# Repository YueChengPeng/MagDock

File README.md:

# MagDock: a modular and customizable tangible inputs interface 

# OVERVIEW

## One Sentence Explanation
A customizable and reconfigurable haptic modular input interface for computers.

## Problem being Solved
Interacting with computers nowadays, either via touchscreens or keyboards (which are basically all buttons) is __BORING__!

The vision is to develop a new input interface, which supports rich interaction inputs and can be configured to be used in various scenarios to boost user experience, promote working efficiency, spark creative expression, enable precise input, provide interesting haptic feedback, etc.

## The Proposed Solution

The input device consists of two parts: a base (left) and various tactile input components (right). To use, simply snap one input component onto the __receptor__ of the base, which can automatically identify the component and read real-time inputs from it.

This input device can be directly used with laptops, pads, phones, etc. But to meet the requirements for the TECHIN514 course, I made a mockup of the computer using Raspberry Pi. To demonstrate the input potentials, I used a drawing web app (using P5.js on the browser of the Raspberry Pi) as a demonstration to showcase the potential of my design in supporting creative expressions (To be more specific, the joystick component is used to move the brush, the slider to adjust the width of the brush, the rotary knob to change the brush color, and the switch to clear the canvas). 

This is just a glimpse of the application! __Other **potential applications** include software extension inputs (e.g. shortcuts in PS, AI, Figma), music controllers/synthesizers (e.g. volume, mix controls), tailored game controllers (e.g. joysticks), sleek controllers for your next robot, etc.

## Working Video
[https://youtu.be/ztausAnTfQE](https://youtu.be/ztausAnTfQE)

# SYSTEM ARCHITECTURE
Details on the sensor device and the display device be elaborated in later sections. This is an overview of how the system architecture looks like:

## Highlights
- _Digital signal processing algorithms_ (explained in the "SENSOR DEVICE" section) are implemented on the ESP32S3 to convert 3-axis magnetic field data to interaction data.
- _BLE communication_ is used between the ESP32S3 XIAO and Raspberry Pi 4B to send real-time interaction data.
- _Websocket communication_ is used to realize real-time bidirectional data communication between the front-end app and the backend Python server.

# SENSOR DEVICE
## BOM
- 1 * [TLV493D magnetometer](https://www.digikey.com/en/products/detail/infineon-technologies/TLV493DA1B6HTSA2/5891933?utm_adgroup=&utm_source=google&utm_medium=cpc&utm_campaign=PMax%20Shopping_Product_High%20ROAS%20Categories&utm_term=&utm_content=&gad_source=1&gclid=Cj0KCQiAwbitBhDIARIsABfFYIIhFqM7H84WtRHeHdwaDSvtmzkl_We-hbJ-xpQ3_GwyePpydjeioHoaAnVZEALw_wcB)
- 1 * [XIAO ESP32S3](https://www.seeedstudio.com/XIAO-ESP32S3-p-5627.html)
- 1 * [2000mAh Lipo battery](https://www.amazon.com/EEMB-2000mAh-Battery-Rechargeable-Connector/dp/B08214DJLJ/ref=sr_1_1?dib=eyJ2IjoiMSJ9.AaRESnG2KaFKBm4vGoJVULr2WB7qFfzYabhQ8Md9-b0vouJRAb8AD5igu6PWXLmkuJEBYbmRwImuKpHJ5pdsRhLyEwjjvQsChCuQ9Ti5hnj9xJeLnhLysFlpADGO_9WMmdDrR2XryqkDcmluJ8wsNDxWuVySQLAJO6v03Y8syoecPRel8-V4ZoHsAkFCZxQORCnmBdP4aBUzIJObcNZi49DLOO0gj_rjCUnFOWYI9McB_vaOh1NP30QFY3F0BmUPpnUr-lxkKe98RbT2v33ip_LxNOVFw7DFMRtKO3Jb8u4.rOgeP4vU8pEIH39cHDtfo4-2HcSZcZEHqHCOB0A5jKM&dib_tag=se&keywords=2000mah+lipo&qid=1709613646&sr=8-1-spons&sp_csd=d2lkZ2V0TmFtZT1zcF9hdGY&psc=1), 1 * [JST-PH 2-Pin SMT Right Angle Connector](https://www.adafruit.com/product/1769?gad_source=1&gclid=CjwKCAiA_5WvBhBAEiwAZtCU75R4XCVwLk1HYnA0MNp8xvJQ45ZHca9OrB8anyndbpKNvk83ktt8_hoCJtcQAvD_BwE) 
- 1 * [Button](https://www.amazon.com/Adafruit-Tactile-Switch-Buttons-square/dp/B00NAY37SK/ref=asc_df_B00NAY37SK/?tag=hyprod-20&linkCode=df0&hvadid=642070594779&hvpos=&hvnetw=g&hvrand=4309338619546982171&hvpone=&hvptwo=&hvqmt=&hvdev=c&hvdvcmdl=&hvlocint=&hvlocphy=9033254&hvtargid=pla-1951385054385&psc=1&mcid=a067f44c1c923892b17863cb8308e844), 1 * [Switch](https://www.digikey.com/en/products/detail/c&k/OS102011MA1QS1/1981431?utm_adgroup=&utm_source=google&utm_medium=cpc&utm_campaign=PMax%20Shopping_Product_Low%20ROAS%20Categories&utm_term=&utm_content=&utm_id=go_cmp-20243063506_adg-_ad-__dev-c_ext-_prd-1981431_sig-CjwKCAiAkp6tBhB5EiwANTCx1A7sPpbNQ89EW0h3bJgkv2yNfTDiOd1HKm84Rqtennji4eYTwqsnyBoCj2gQAvD_BwE&gad_source=1&gclid=CjwKCAiAkp6tBhB5EiwANTCx1A7sPpbNQ89EW0h3bJgkv2yNfTDiOd1HKm84Rqtennji4eYTwqsnyBoCj2gQAvD_BwE)
- 1 * [LS R976 SMD LED](https://www.digikey.com/en/products/detail/ams-osram-usa-inc./LS%2520R976-NR-1-0-20-R18/1642798?utm_adgroup=&utm_source=google&utm_medium=cpc&utm_campaign=PMax%20Shopping_Product_Medium%20ROAS%20Categories&utm_term=&utm_content=&utm_id=go_cmp-20223376311_adg-_ad-__dev-c_ext-_prd-1642798_sig-CjwKCAiA_5WvBhBAEiwAZtCU73qnJ3SjxQmnfvGEfz_Vjte8sVrvr7AMyYXotjacGVyFfUPCos_6uxoCeiEQAvD_BwE&gad_source=1&gclid=CjwKCAiA_5WvBhBAEiwAZtCU73qnJ3SjxQmnfvGEfz_Vjte8sVrvr7AMyYXotjacGVyFfUPCos_6uxoCeiEQAvD_BwE)
- SMD resistors and capacitors
- Magnets (8mm and 3mm)
- 5mm Acrylic sheet for enclosure
## Schematic Diagram

## Gallery

## Details
### 🧲 🧲 ❤️ it's all about magnets ❤️ 🧲 🧲
Magnets, magnets, magnets, magnets! Hooray!
In this project, magnets are without doubt the protagonist! It's used as:
- Providing __haptic feedback__ on the input components (inspired by [Mechamagnets](https://clementzheng.info/Mechamagnets)).
- Providing the __snapping force__ between the input components and the sensor base.
- Serving as the __conductor__. As shown in the image, each input component has a resistor embedded in it - it's a cheap and simple alternative to NFC tags - __it allows the sensor device to identify which component is attached to the base__. The resistor is snap to the magnet, which in turn snap to the screws fixed on the main PCB, thus forming a conductive path. Then, a simple voltage divider circuit is enough to let the MCU recognize different input components.
- Serving as the __input trigger__: when users interact with the inputs, the position of certain embedded magnets will change, enabling the 3-axis hall effect sensor to track its interaction state.

### DSP to convert 3-axis magnetic field data to interaction data

Each input component has three kinds of magnets:
- Haptic feedback provider.
- "Snapper" to base.
- Input trigger.

The input trigger moves along with the moving part of the input component, causing the magnetic field to change:

Yes.. but how to interpret the raw three-axis magnetic field data?

- Firstly the raw data goes through a moving average filter.
- Then, for discrete inputs (including _slider_, _rotary knob_, and _toggle switch_), I documented the average reading of the TLV493D sensor with the input component's moving part in different positions. Then, given a new reading from the sensor, the algorithm will find the shortest Euclidean distance between the new vector and pre-collected vectors in the dataset, thus identifying the moving part's position. This algorithm is inspired by the RAG method (the vector in this case is text embeddings) in the LLM.
- For continuous inputs (the _joystick_), I documented the sensor reading with the joystick pointing in different directions. The results were typical sinusoidal functions in the x and y direction (the Bx and By are used to configure the direction of the joystick, while the Bz is used to identify whether the joystick is moved away from the center point). Therefore, given a By and Bx value, I can first compare the Bx with the baseline to tell whether it's in [0, pi] or [pi, 2pi], then by calculating `arccos(By)`, I can get the solution of the angle of the joystick.

In conclusion, this sensor device features a single sensor for configuring diverse inputs from different input devices.

# DISPLAY DEVICE
## BOM
- 1 * [Raspberry Pi 4B](https://www.raspberrypi.com/products/raspberry-pi-4-model-b/)
- 1 * [7inch Display](https://www.amazon.com/dp/B097H277WS?ref_=cm_sw_r_apin_dp_H4QJ45A799ZPF6NZQ4QH&language=en-US&th=1)
- 1 * [Stepper motor gauge](https://www.adafruit.com/product/2424)
- 1 * Button
- 1 * LED
- Several JST connectors
- 1.5mm Acrylic sheet for enclosure

## Schematic Diagram

## Gallery

## Details
The display device is built around the Raspberry Pi. It runs a Python backend and a frontend using P5.js. The Python reads inputs from a button (capture screenshot) and controls the x27 stepper motor directly via four GPIOs (which is not safe to do so, but the x27 stepper motor consumes little current and is safe to drive using mere GPIOs on the Raspberry Pi. Otherwise H-Bridge should be used, such as the TB6612 IC). The needle of the motor indicates the current stroke width of the brush. A 7-inch LCD display is plugged into the Raspberry Pi using an HDMI cable to show the canvas of the P5.js. An LED is used to indicate if the button is pressed and a screenshot is captured.

# BATTERY CONSIDERATIONS
## Sensor Device

### usage modes
- __Sleep: if the sensor detects no reading change for 5 min, switch to sleep mode. In this mode, 20% of the time will be used to be Active without BLE (to detect whether there is a reading change); and 80% of the time will be in deep sleep.
- __Sensing__: active sensing mode, collect sensor data and send data to display device via BLE. In this mode, the MCU would always be active with BLE to guarantee a fluent user experience.
### reflections
- As a peripheral device of computers like keyboards and mice, I want my device can be used for around a week without charging. So I determine my "days of use" metric based on my application scenario.
- Any battery size under 10cm * 5cm is acceptable since my device is something you would put on the table for a long time, but not carry with you a lot. I also made the size of my sensing device relatively large because in this way users can better interact with those tangible inputs, allowing it to provide a better hand feel.
- The battery tradeoff: although the battery size can be relatively large, the major consideration would be the cost (larger battery capacity, more expensive). So the first tradeoff I made would be to choose a 2000mAh Lipo battery, which balances cost and battery capacity. 
- Other potential tradeoffs can be: when the data transfer rate is low, the power consumption will be low as well, but in my application case, it’ll cause a negative user experience, which can be an important tradeoff.
- After analyzing my power, I learned that both the processor and sensor can run on very low energy consumption modes (some sensors provide low power modes as well). These features can be used to optimize power consumption. 

## Display Device

### usage modes
- __Idle mode__: not receiving data from the processor for 5 minutes, idle the Pi and disable HDMI (turn the screen off) to save power
    - Raspberry Pi itself doesn’t have a low power/sleep mode and requires extra hardware https://spellfoundry.com/sleepy-pi/sleepy-pi-faq/
- __Interactive mode__: perform intended drawing functionalities (receive sensor data, plot graph via p5.js, and other interactive inputs/outputs: e.g. LED, button, and stepper motor).

### reflections
- After analyzing, I found that Raspberry Pi consumes TONS of power, and it is also very picky on the power supply: the Pi4B requires a good quality USB-C power supply capable of delivering 5V at 3A https://github.com/YueChengPeng/MagDocker/blob/main/datasheet/raspberry-pi-4-datasheet.pdf. I found no Lipo battery or power bank that can supply a current this large. Therefore, it’s better to power it directly via USB-C power cables but not batteries. A good display also consumes a lot of power. Given that, the "days of use" will be "forever" as long as you have the power plugged in.

- The usage of power cables is a good tradeoff considering user experience.
    - _Cost_: large-capacity batteries (even imagine there does exist one that supports 3A output) are obviously more expensive than a simple USB-C charger.
    - _Portability_: small size (lightweight) and large capacity (work longer) obviously cannot be achieved at the same time. If we want the Pi to work longer, the battery size will hinder better portability. But with the USB-C charger, this will be a non-issue.

# BUDGET SUMMARY
| Sensor Device Components                 | Price | Number | Total Price |
|------------------------------------------|-------|--------|-------------|
| XIAO ESP32S3                             | 7.49  | 1      | 7.49        |
| 2000mAh Lipo battery                     | 13.99 | 1      | 13.99       |
| Button                                   | 0.5   | 1      | 0.5         |
| Switch                                   | 0.64  | 1      | 0.64        |
| SMD LED                                  | 0.27  | 1      | 0.27        |
| TLV493DA1B6HTSA2                         | 1.5   | 1      | 1.5         |
| JST-PH 2-Pin SMT Right Angle Connector   | 0.75  | 1      | 0.75        |
| Acrylic enclosure                        | 18.99 | 1      | 18.99       |
| Magnets (8mm and 3mm)                    | 12    | 1      | 12          |
| Resistors & Capacitors                   | 0.5   | 1      | 0.5         |
| **Sum**                                  |       |        | **56.63**   |

| Display Device Components                | Price | Number | Total Price |
|------------------------------------------|-------|--------|-------------|
| Raspberry Pi 4B                          | 35    | 1      | 35          |
| stepper motor                            | 5     | 1      | 5           |
| Button                                   | 0.5   | 1      | 0.5         |
| LED                                      | 0.4   | 1      | 0.4         |
| JST connectors                           | 1     | 1      | 1           |
| 7inch display                            | 45.99 | 1      | 45.99       |
| Acrylic enclosure                        | 5     | 1      | 5           |
| **Sum**                                  |       |        | **92.89**   |

| **Total Sum**                            | 149.52    |
|------------------------------------------|-----------|
| **Total Sum Purchased by GIX**           | 97.32     |

# FUTURE WORKS
- Enrich the tangible input components library.
- Change the component identification mechanism: maybe small NFC tags are strong substitutions.
- Increase receptors of the sensor base! Originally I envisioned something like the dock on the IOS/MacOS that consisted of a long receptor of many icons (components, in my case). Due to the time limit, I could only implement a version with only one receptor. It will definitely be interesting to have a, e.g. four receptor base, where users can configure different combinations of components under different work scenarios.
- Fully open source my design and provide more detailed steps to replicate this work. Also include a user guide on how to design the user's tangible inputs (e.g. the middle "haptic" layer of the input components can be changed on the fly to configure different haptic feedback).
- Implement a driver software, so that this input interface can be used on software on my computer. In the software, users can dynamically reconfigure the DSP algorithm for their customized components.

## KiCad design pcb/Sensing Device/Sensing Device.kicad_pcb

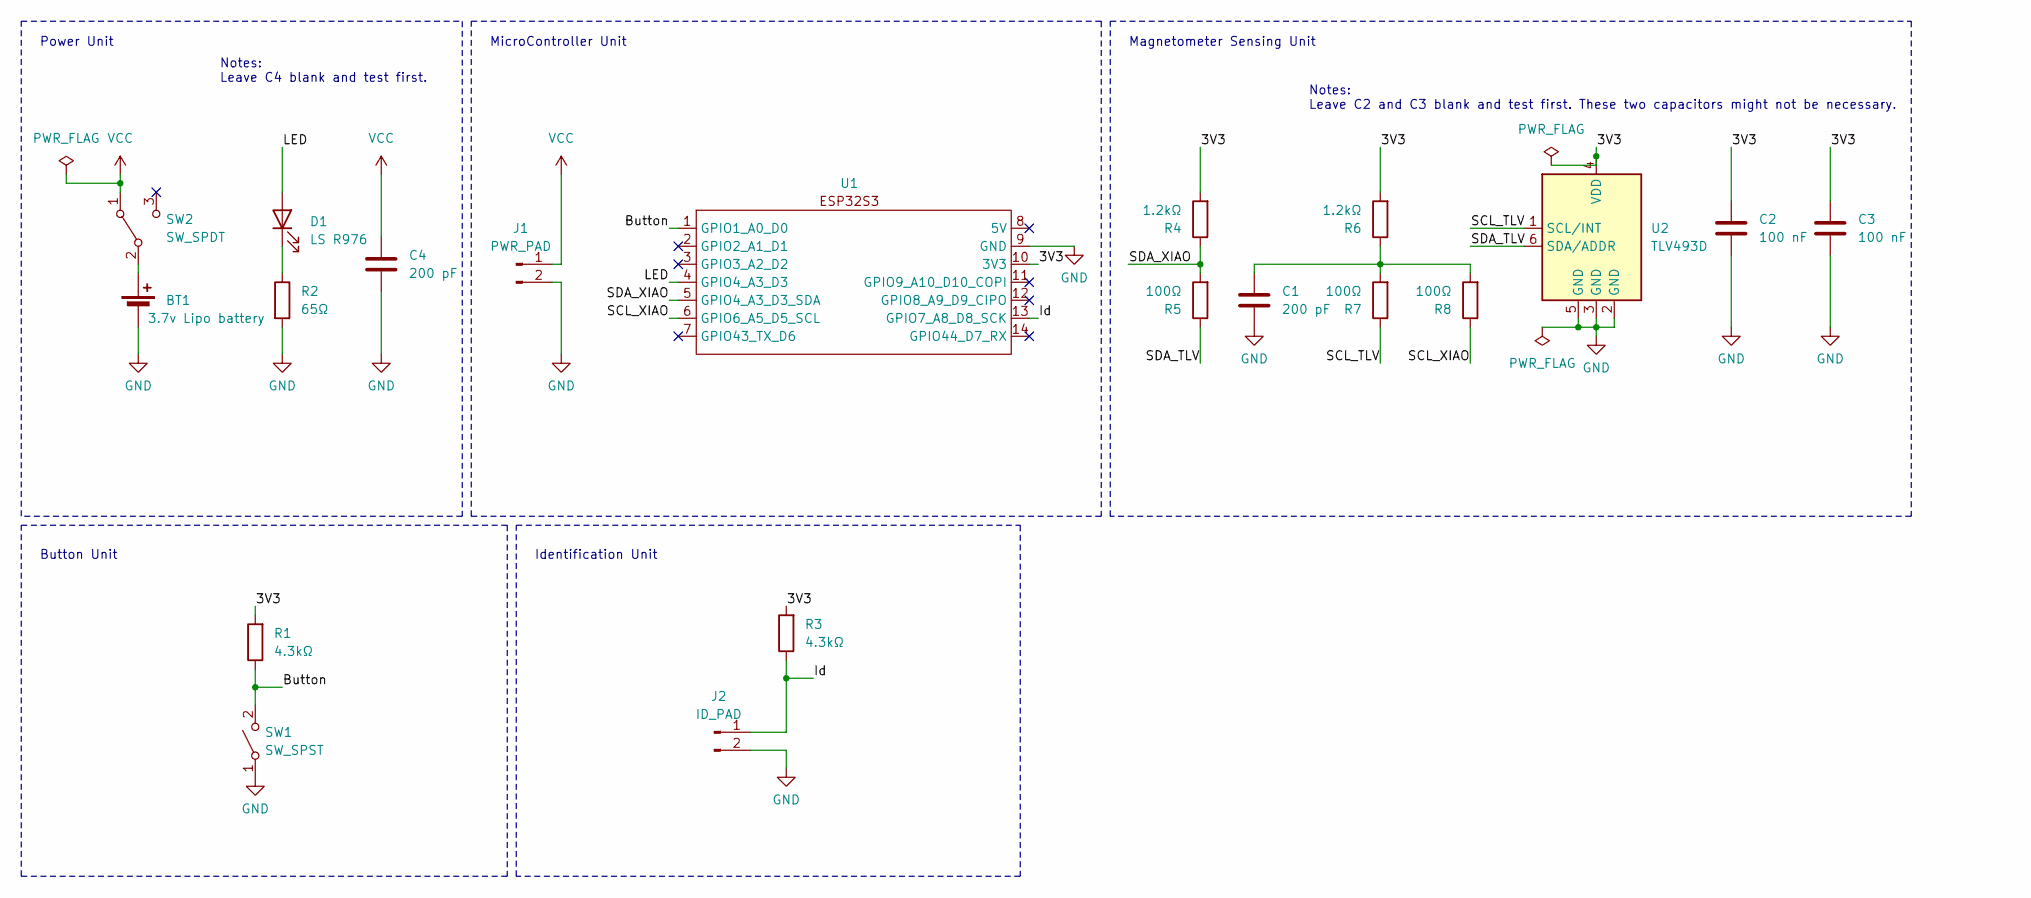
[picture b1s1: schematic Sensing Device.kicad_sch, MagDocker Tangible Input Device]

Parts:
BT1: 3.7v Lipo battery; JST_ZE_SM02B-ZESS-TB_1x02-1MP_P1.50mm_Horizontal
C1, C4: 200 pF; C_0805_2012Metric_Pad1.18x1.45mm_HandSolder
C2, C3: 100 nF; C_0805_2012Metric_Pad1.18x1.45mm_HandSolder
D1: LS R976; LED_0805_2012Metric_Pad1.15x1.40mm_HandSolder
J1: PWR_PAD; JST_NV_B02P-NV_1x02_P5.00mm_Vertical
J2: ID_PAD; 40mm_rectangle_M3
R1, R3: 4.3kΩ; R_0805_2012Metric_Pad1.20x1.40mm_HandSolder
R2: 65Ω; R_0805_2012Metric_Pad1.20x1.40mm_HandSolder
R4, R6: 1.2kΩ; R_0805_2012Metric_Pad1.20x1.40mm_HandSolder
R5, R7, R8: 100Ω; R_0805_2012Metric_Pad1.20x1.40mm_HandSolder
SW1: SW_SPST; SW_PUSH-12mm
SW2: SW_SPDT; SWITCH_THT_SPDT_11MA1QS1
U1: XIAO_ESP32_SENSE
U2: TLV493D; SOT-23-6

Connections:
/3V3: C2.1, C3.1, R1.2, R3.2, R4.2, R6.2, U1.10 (3V3), U2.4 (VDD)
/Button: R1.1, SW1.2 (B), U1.1 (GPIO1_A0_D0)
/Id: J2.1, R3.1, U1.13 (GPIO7_A8_D8_SCK)
/LED: D1.2 (A), U1.4 (GPIO4_A3_D3)
/SCL_TLV: R7.1, U2.1 (SCL/INT)
/SCL_XIAO: R8.1, U1.6 (GPIO6_A5_D5_SCL)
/SDA_TLV: R5.1, U2.6 (SDA/ADDR)
/SDA_XIAO: R4.1, R5.2, U1.5 (GPIO4_A3_D3_SDA)
GND: BT1.2 (-), C1.2, C2.2, C3.2, C4.2, J1.2, J2.2, R2.2, SW1.1 (A), U1.9 (GND), U2.2 (GND), U2.3 (GND), U2.5 (GND)
unnamed: BT1.1 (+), SW2.2 (B)
unnamed: C1.1, R6.1, R7.2, R8.2
unnamed: D1.1 (K), R2.1
VCC: C4.1, J1.1, SW2.1 (A)

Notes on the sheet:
Notes: Leave C4 blank and test first.
Notes: Leave C2 and C3 blank and test first. These two capacitors might not be necessary.
Power Unit
MicroController Unit
Magnetometer Sensing Unit
Button Unit
Identification Unit

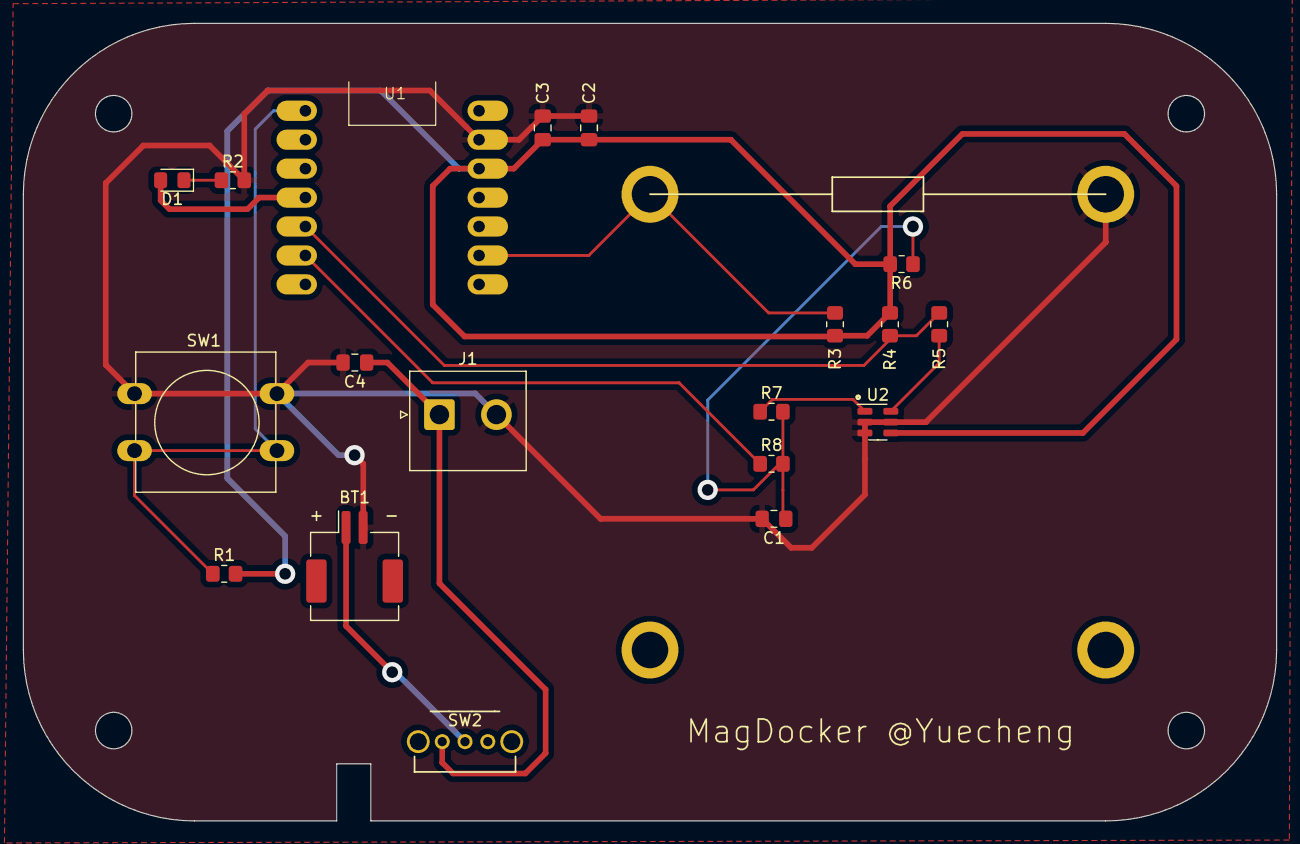
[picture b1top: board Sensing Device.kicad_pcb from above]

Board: 2 copper layers, 110.0 x 70.0 mm, 20 parts (0 on the bottom side), 13 nets.

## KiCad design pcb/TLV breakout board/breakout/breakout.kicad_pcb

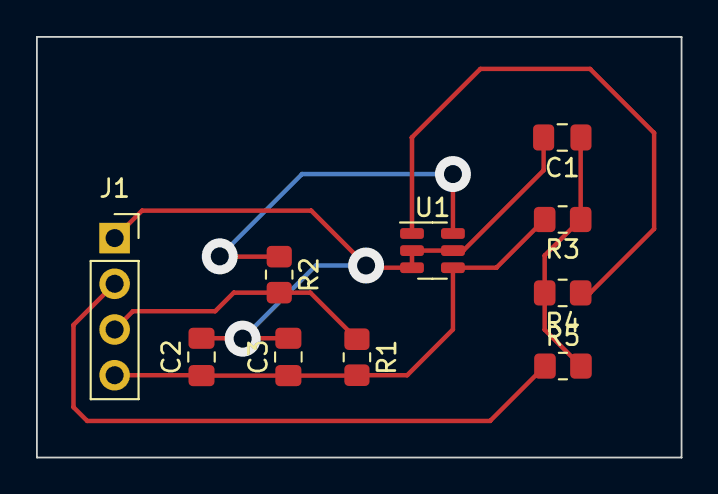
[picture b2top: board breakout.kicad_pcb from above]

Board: 2 copper layers, 35.8 x 23.4 mm, 10 parts (0 on the bottom side), 7 nets.

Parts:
C1, C2, C3: 100 nF; C_0805_2012Metric_Pad1.18x1.45mm_HandSolder
J1: Conn_01x04; PinSocket_1x04_P2.54mm_Vertical
R1, R3: 1.2kΩ; R_0805_2012Metric_Pad1.20x1.40mm_HandSolder
R2, R4, R5: 100Ω; R_0805_2012Metric_Pad1.20x1.40mm_HandSolder
U1: TLV493D; SOT-23-6

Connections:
/3V3: C2.1, C3.1, J1.4, R1.2, R3.2, U1.4 (VDD)
/SCL_TLV: R4.1, U1.1 (SCL/INT)
/SCL_XIAO: J1.2, R5.1
/SDA_TLV: R2.1, U1.6 (SDA/ADDR)
/SDA_XIAO: J1.3, R1.1, R2.2
GND: C1.2, C2.2, C3.2, J1.1, U1.2 (GND), U1.3 (GND), U1.5 (GND)
unnamed: C1.1, R3.1, R4.2, R5.2

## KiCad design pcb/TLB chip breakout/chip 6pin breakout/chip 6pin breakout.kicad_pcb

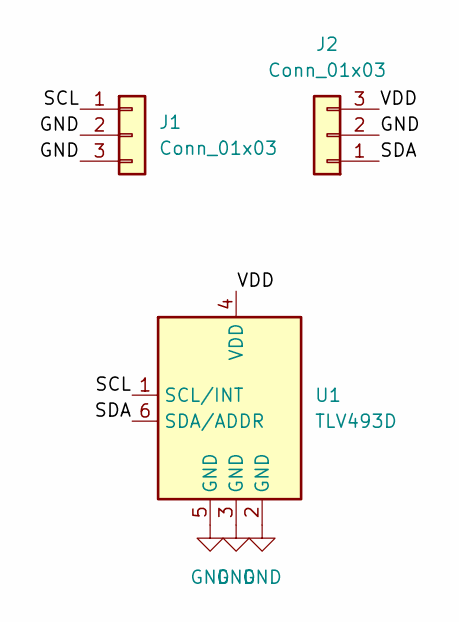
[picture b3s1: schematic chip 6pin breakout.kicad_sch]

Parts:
J1, J2: Conn_01x03; PinHeader_1x03_P2.54mm_Vertical
U1: TLV493D; SOT-23-6

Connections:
/SCL: J1.1, U1.1 (SCL/INT)
/SDA: J2.1, U1.6 (SDA/ADDR)
/VDD: J2.3, U1.4 (VDD)
GND: J1.2, J1.3, J2.2, U1.2 (GND), U1.3 (GND), U1.5 (GND)

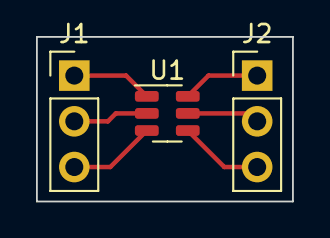
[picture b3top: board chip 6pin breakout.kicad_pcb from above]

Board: 2 copper layers, 14.2 x 9.1 mm, 3 parts (0 on the bottom side), 4 nets.

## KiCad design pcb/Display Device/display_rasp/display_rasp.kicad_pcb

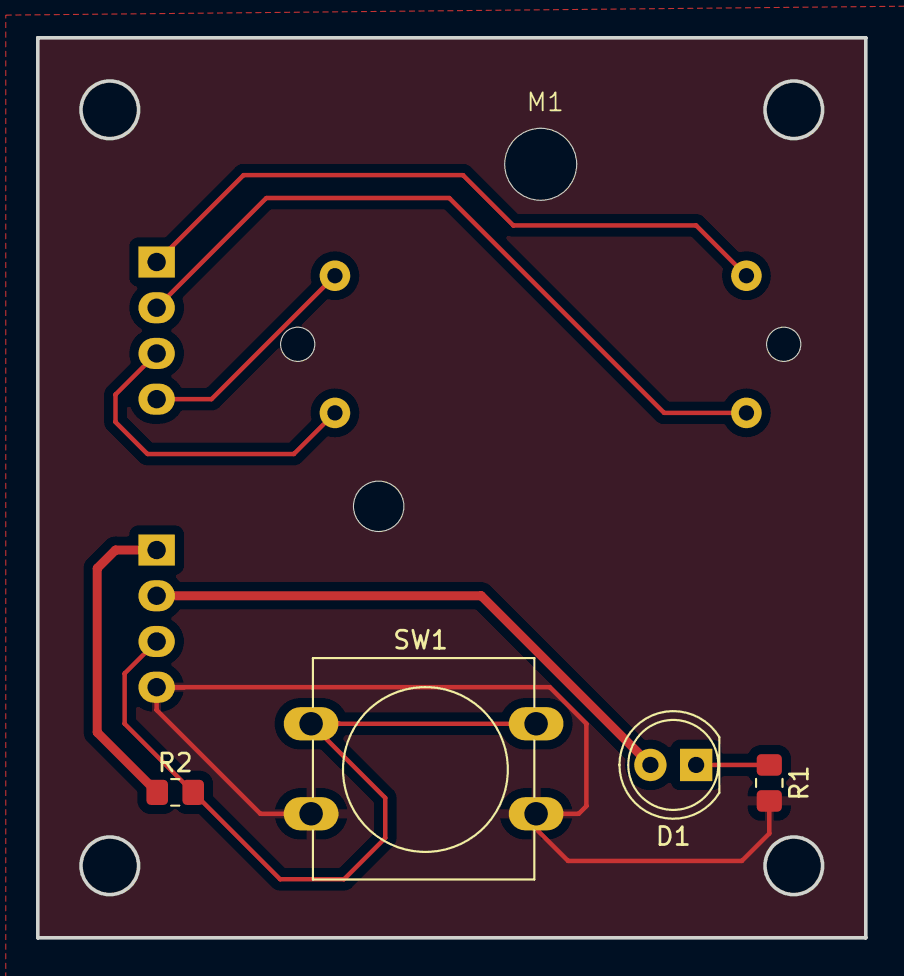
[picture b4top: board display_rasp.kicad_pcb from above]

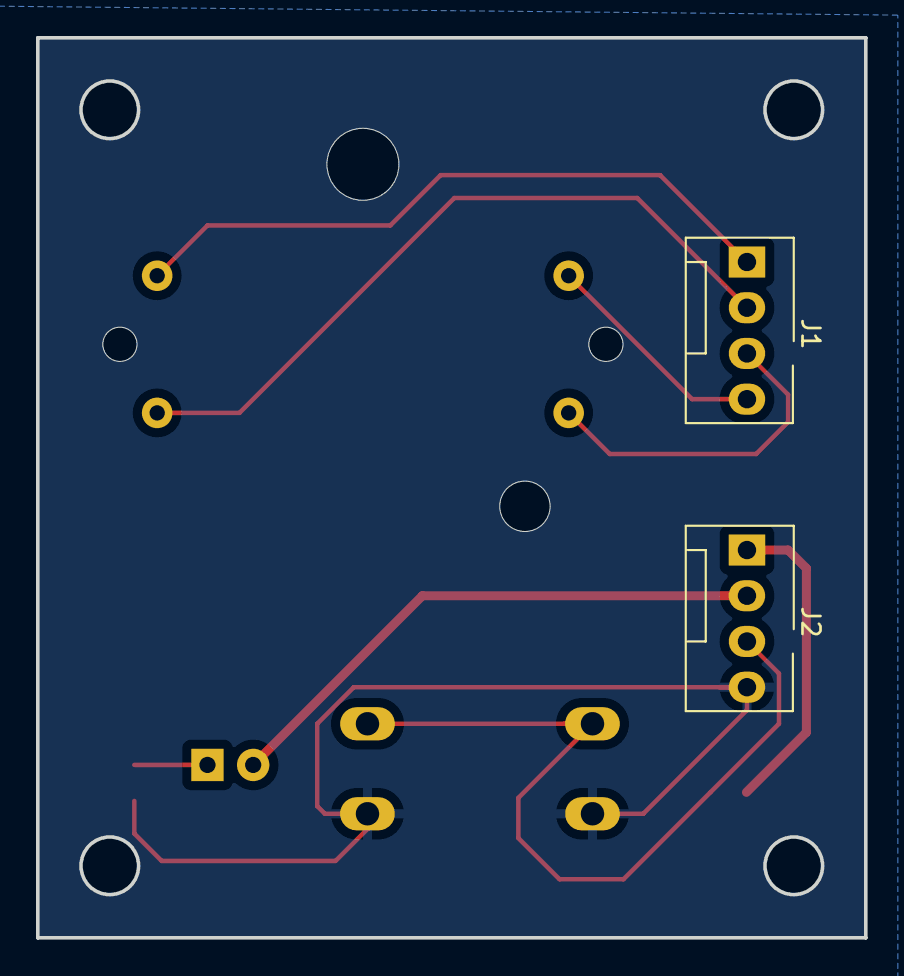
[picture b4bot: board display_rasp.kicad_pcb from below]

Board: 2 copper layers, 46.0 x 50.0 mm, 7 parts (2 on the bottom side), 9 nets.

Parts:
D1: LED; LED_D5.0mm
J1, J2: Conn_01x04; FanPinHeader_1x04_P2.54mm_Vertical
M1: Stepper_Motor_bipolar; x27_stepper
R1, R2: R; R_0805_2012Metric_Pad1.20x1.40mm_HandSolder
SW1: SW_SPST; SW_PUSH-12mm

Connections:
/BUTTON: J2.3, R2.2, SW1.1 (A)
/GPIO17: J1.1, M1.1
/GPIO22: J1.3, M1.3
/GPIO23: J1.4, M1.4
/GPIO27: J1.2, M1.2 (-)
/LED: D1.2 (A), J2.2
/VCC: J2.1, R2.1
GND: J2.4, R1.2, SW1.2 (B)
unnamed: D1.1 (K), R1.1

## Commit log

2024-01-16 communication diagram change
2024-01-17 schematic
2024-01-18 schematic update
2024-01-22 pcb update
2024-02-01 datasheet
2024-02-01 pwr sheet
2024-02-02 power management
2024-03-05 readme
